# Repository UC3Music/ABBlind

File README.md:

ABBlind
--------------------------

Device to make random blind tests to audio equipment.

Why to spend lots of money in audiophile quality devices when you cannot tell the different from a more affordable device? ABBlind allows you to make blind tests for you to try to distinguish between two audio devices. It will randomly present you channels A and B, without telling you which channel are you listening to until you have heard three samples. Then, it will tell you in which order you listened to devices A and B.

As it is based on Arduino, you can modify ABBlind to add custom testing modes and more functionality.

## v0.1 Prototype
### Assembled

### PCBs

## Firmware
### mbed version
Sources available at: https://developer.mbed.org/users/def/code/ABBlind/
# Credits
* Author: [David Estevez Fernandez](https://github.com/David-Estevez)

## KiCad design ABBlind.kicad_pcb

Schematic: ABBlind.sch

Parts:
BRD1: ARDUINO_UNO
C1: C; C_0805_HandSoldering
C2: 0.1-1uF X5R; C_0805_HandSoldering
C3: 1uF X5R; C_0805_HandSoldering
C4, C5: 0.1uF; C_0805_HandSoldering
D1, D2, D3: LED_BICOLOR
J1, J2, J3: JACK_FEMALE_STEREO_6_PINS; Conn_Jack_Female_635_THD
R1, R2, R3, R4, R5, R6: R; R_0805_HandSoldering
SW1, SW2: SW_PUSH; Switches-Push_switch_THD
U1, U2: TS5A22364
U3: TLV70033DDCT; SOT-23-5

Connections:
+3V3: C3.2, C4.2, C5.2, U1.1 (VCC), U2.1 (VCC), U3.5 (Vout)
+5V: BRD1.26 (5V), C2.2, U3.1 (Vin), U3.3 (EN)
/AUDIO_CNTRL: BRD1.19 (A3), U1.5 (IN), U1.7 (IN), U2.5 (IN), U2.7 (IN)
/FOOTSWITCH: BRD1.3 (2), SW1.2
/GND_A: J2.S, U1.8 (NC), U2.8 (NC)
/GND_B: J3.S, U1.10 (NO), U2.10 (NO)
/GND_OUT: J1.S, U1.9 (COM), U2.9 (COM)
/LED_1_1: BRD1.4 (3(PWM)), R1.1
/LED_1_2: BRD1.6 (5(PWM)), R2.1
/LED_2_1: BRD1.7 (6(PWM)), R3.1
/LED_2_2: BRD1.10 (9(PWM)), R4.1
/LED_3_1: BRD1.11 (10(PWM-SS)), R5.1
/LED_3_2: BRD1.12 (11(PWM-MOSI)), R6.1
/LEFT_A: J2.T, U2.4 (NC)
/LEFT_B: J3.T, U2.2 (NO)
/LEFT_OUT: J1.T, U2.3 (COM)
/RIGHT_A: J2.R, U1.4 (NC)
/RIGHT_B: J3.R, U1.2 (NO)
/RIGHT_OUT: J1.R, U1.3 (COM)
/~RESET: BRD1.28 (~RESET), C1.1, SW2.1
GND: BRD1.15 (GND), BRD1.24 (GND), BRD1.25 (GND), C1.2, C2.1, C3.1, C4.1, C5.1, D1.1 (K), D1.3 (K), D2.1 (K), D2.3 (K), D3.1 (K), D3.3 (K), SW1.1, SW2.2, U1.6 (GND), U2.6 (GND), U3.2 (GND)
unnamed: D1.2 (A), R2.2
unnamed: D1.4 (A), R1.2
unnamed: D2.2 (A), R4.2
unnamed: D2.4 (A), R3.2
unnamed: D3.2 (A), R6.2
unnamed: D3.4 (A), R5.2

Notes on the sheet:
INPUT A
INPUT B
OUTPUT
TI recommeds a 0.1uF bypass cap near supply

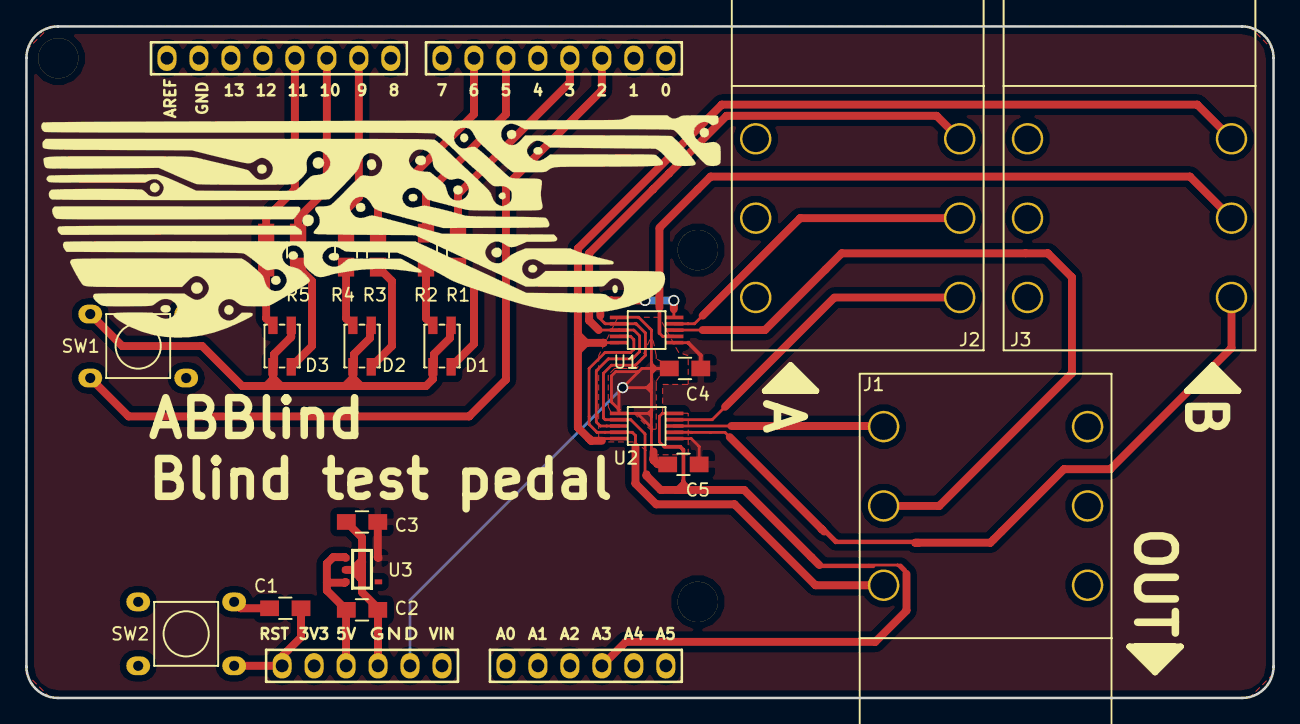
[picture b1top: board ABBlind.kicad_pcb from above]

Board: 2 copper layers, 99.1 x 53.3 mm, 23 parts (0 on the bottom side), 27 nets.

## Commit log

2015-07-18 Add analog switch module
2015-07-23 Add hammond box CAD files
2015-08-09 Finished v0.1 schematic
2015-08-11 Add footprint and symbol for LED bicolor
2015-08-16 Started working on the PCB
2015-08-18 Routing almost finished
2015-08-19 Finish PCB routing
2015-08-31 Round edges
2015-08-31 Prototype 1 - v0.1
2015-08-31 Add useful files
2015-08-31 Add README.md
2015-10-27 Pre-fabrication v1.0
2015-10-27 Add gerber files
2015-11-04 Fix library path
2015-11-04 Add BOM file
2015-11-09 Add gitignore
2015-11-10 Move files to hardware
2015-11-10 Add gitignore file
2015-11-10 Add images to doc
2015-11-10 Add cool README file
2015-11-15 Fix BOM
2015-11-22 Add datasheet
2015-11-27 Add program to do a basic test of the hardware
2015-11-30 Add code to switch audio
2015-11-30 Add images of prototype
2015-12-05 Move Arduino files
2015-12-05 Enable audio toggling
2015-12-05 Add binary firmware for hardware test
2015-12-05 Add firmware download info to README
2015-12-05 Add mbed sources for ABBlind hardware test
2016-01-30 Update README with programming instructions
2016-09-21 Add binary for v1.0 firmware
2016-09-22 Add v1.0 firmware exported from mbed website
2016-09-22 Edit link to point to new mbed repo
2019-03-12 Good boy scout
